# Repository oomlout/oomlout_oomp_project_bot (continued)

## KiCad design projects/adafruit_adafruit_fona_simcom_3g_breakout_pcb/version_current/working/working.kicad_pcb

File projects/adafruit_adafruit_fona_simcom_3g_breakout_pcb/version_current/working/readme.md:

# Adafruit-FONA-SIMCOM-3G-Breakout-PCB by adafruit  
This is a harvested standardized copy of a project from github.  
The original project can be found at:  
https://github.com/adafruit/Adafruit-FONA-SIMCOM-3G-Breakout-PCB  
Please consult that link for additional, details, files, and license information.  
Note: It was auto harvested and if the original repo had more than one board file or anything out of the ordinary the files here are likely not representative.

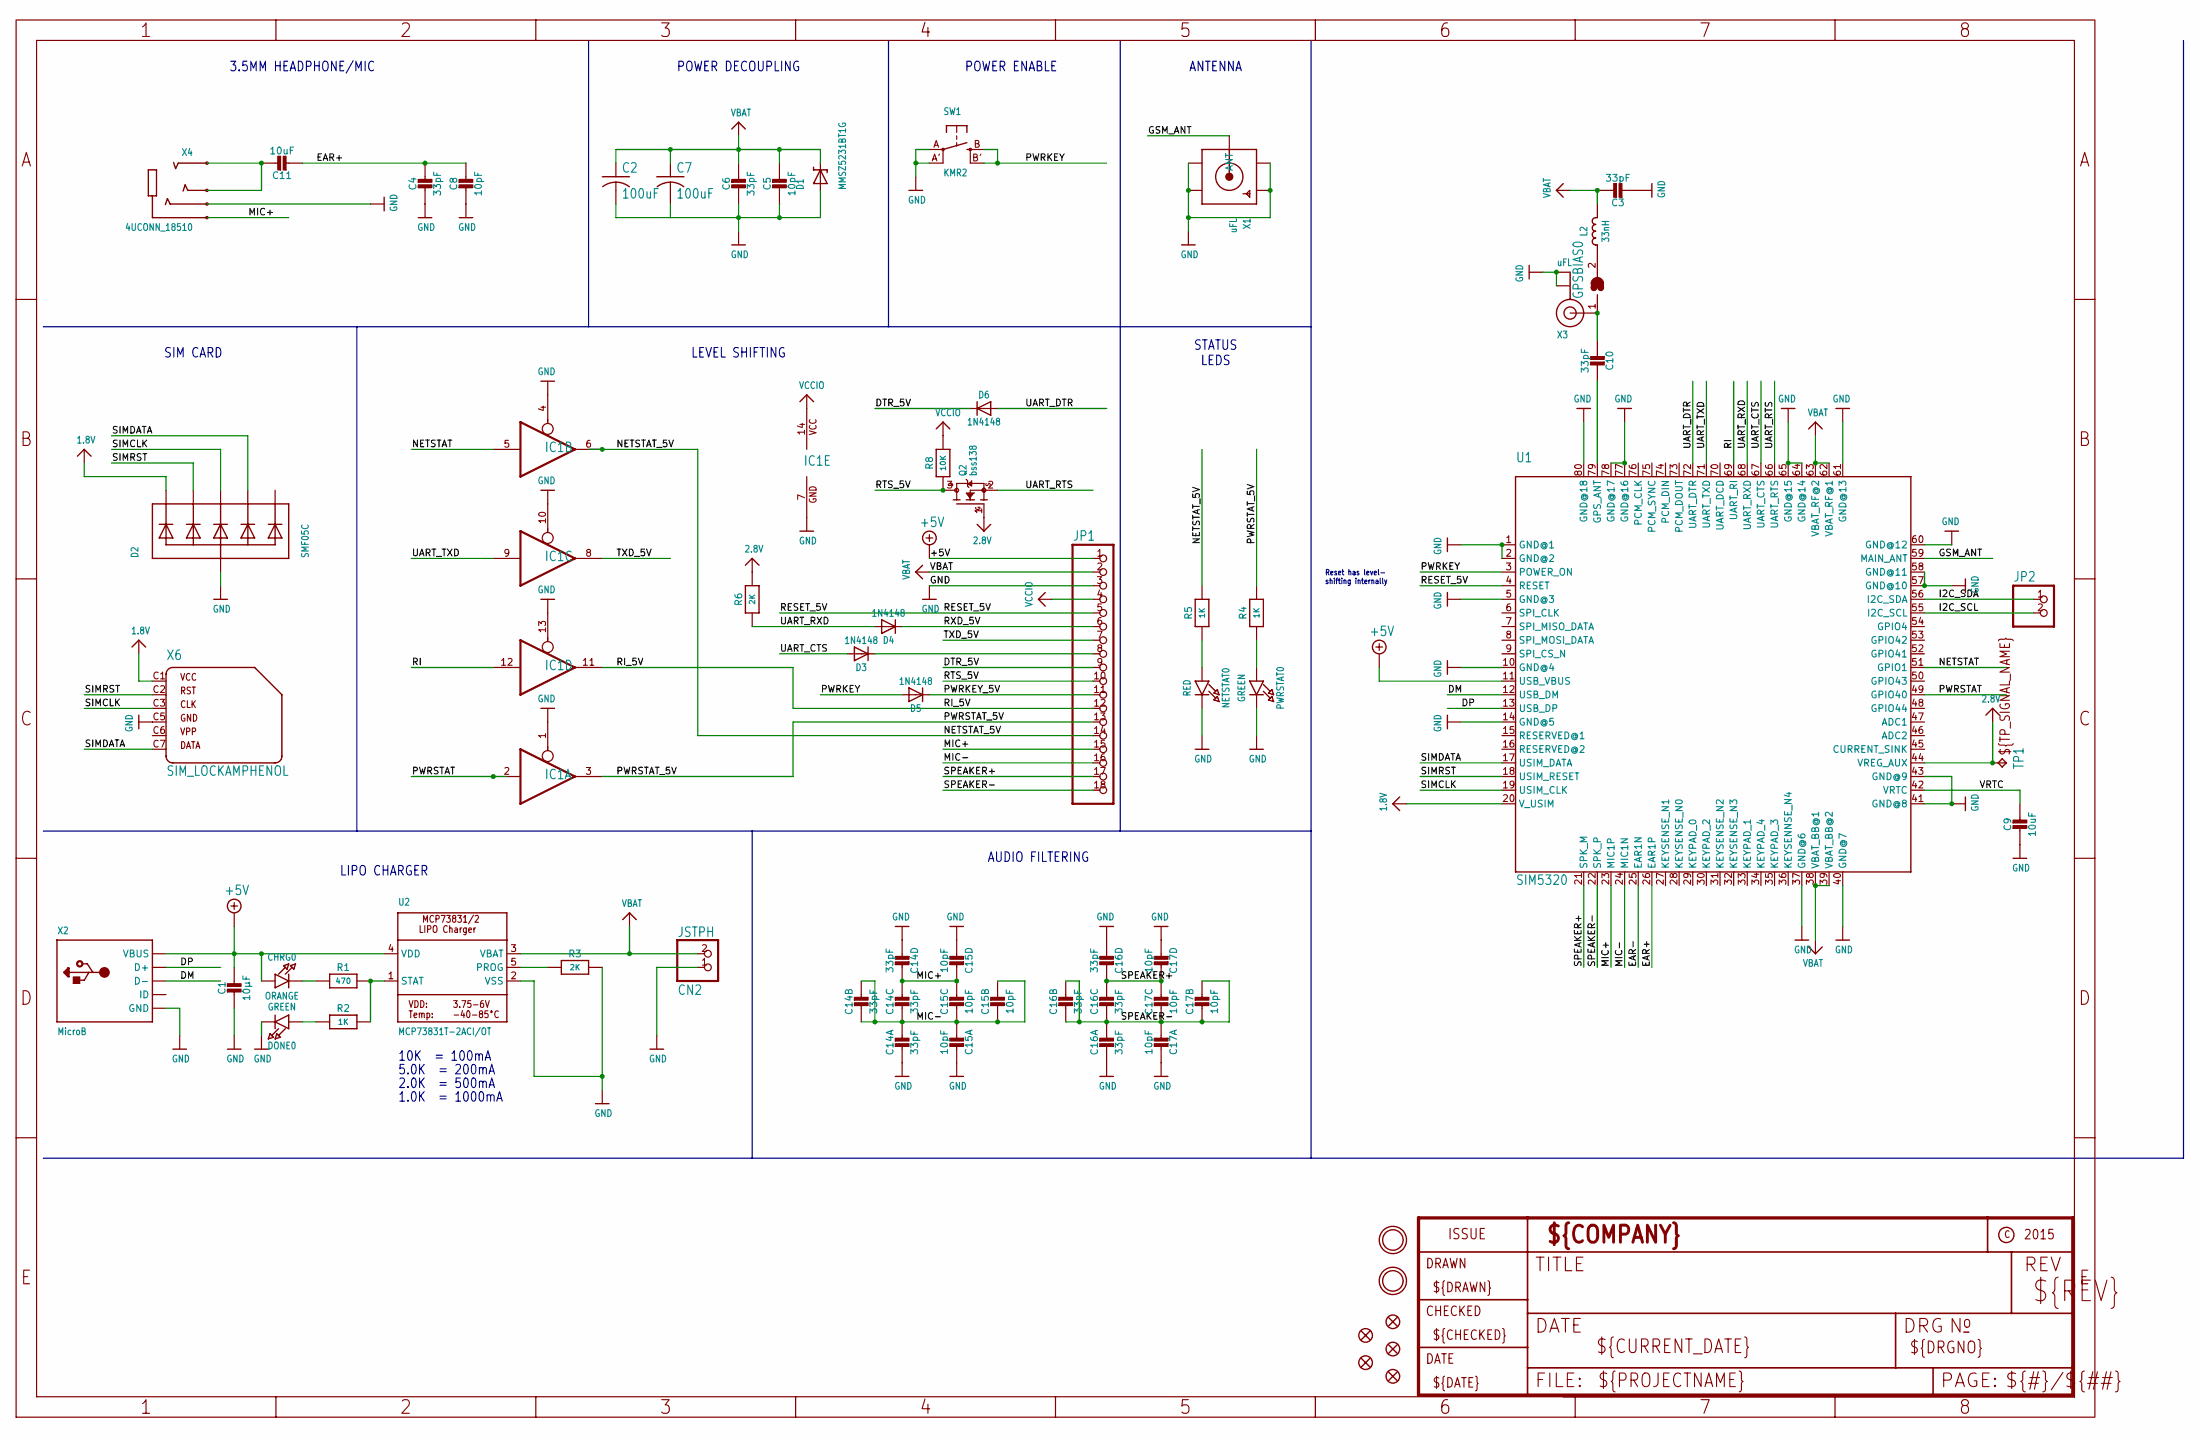
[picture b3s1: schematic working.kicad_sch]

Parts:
C1: 10µF; 0805-NO
C2, C7: 100uF; C1210
C3, C4, C6, C10: 33pF; 0805-NO
C5, C8: 10pF; 0805-NO
C9, C11: 10uF; 0805-NO
C14, C16: 33pF; RESPACK_4X0603
C15, C17: 10pF; RESPACK_4X0603
CHRG0: ORANGE; CHIPLED_0805_NOOUTLINE
CN2: JSTPH; JSTPH2
D1: MMSZ5231BT1G; SOD-123
D2: SMF05C; SOT363
D3, D4, D5, D6: 1N4148; SOD-323
DONE0: GREEN; CHIPLED_0805_NOOUTLINE
FID1, FID2, FID3, FID4, FID5: FIDUCIAL""; FIDUCIAL_1MM
GPSBIAS0: SOLDERJUMPER; SOLDERJUMPER_ARROW_NOPASTE
IC1: 74125PW; TSSOP14
JP1: HEADER-1X18; 1X18_ROUND70
JP2: HEADER-1X2ROUND; 1X02_ROUND
L2: 33nH; _0805MP
NETSTAT0: RED; CHIPLED_0805_NOOUTLINE
PWRSTAT0: GREEN; CHIPLED_0805_NOOUTLINE
Q2: bss138; SOT23-WIDE
R1: 470; 0805-NO
R2, R4, R5: 1K; 0805-NO
R3, R6: 2K; 0805-NO
R8: 10K; 0805-NO
SW1: KMR2; BTN_KMR2_4.6X2.8
TP1: TPTP11R; TP11R
U1: SIM5320
U2: MCP73831T-2ACI/OT; SOT23-5
U$33, U$34: MOUNTINGHOLE2.5; MOUNTINGHOLE_2.5_PLATED
X1: uFL; SMA_EDGELAUNCH_UFL
X2: MicroB; 4UCONN_20329
X3: uFL; U.FL
X4: 4UCONN_18510
X6: SIM_LOCKAMPHENOL; C707_10M006_512_2

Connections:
1.8V: D2.1 (C1), U1.20 (V_USIM), X6.C1 (1)
2.8V: Q2.1 (G), R6.2, TP1.TP, U1.44 (VREG_AUX)
+5V: C1.1, CHRG0.A, JP1.1, U1.11 (USB_VBUS), U2.4 (VDD), X2.VBUS
CTS_5V: D3.C, JP1.8
DM: U1.12 (USB_DM), X2.D-
DP: U1.13 (USB_DP), X2.D+
DTR_5V: D6.C, JP1.9
EAR+: C4.1, C8.1, C11.2, U1.26 (EAR1P)
EAR-: U1.25 (EAR1N)
GND: C1.2, C2.2, C3.2, C4.2, C5.2, C6.2, C7.2, C8.2, C9.2, C14.5 (2), C14.8 (2), C15.4 (1), C15.8 (2), C16.5 (2), C16.8 (2), C17.4 (1), C17.8 (2), CN2.1, D1.A, D2.2 (A), DONE0.C, IC1.1 (OE), IC1.4 (OE), IC1.7 (GND), IC1.10 (OE), IC1.13 (OE), JP1.3, NETSTAT0.C, PWRSTAT0.C, R3.2, SW1.A, SW1.A' (P1), U1.1 (GND@1), U1.2 (GND@2), U1.5 (GND@3), U1.10 (GND@4), U1.14 (GND@5), U1.37 (GND@6), U1.40 (GND@7), U1.41 (GND@8), U1.43 (GND@9), U1.57 (GND@10), U1.58 (GND@11), U1.60 (GND@12), U1.61 (GND@13), U1.64 (GND@14), U1.65 (GND@15), U1.77 (GND@16), U1.78 (GND@17), U1.80 (GND@18), U2.2 (VSS), X1.GND@1 (GND1), X1.GND@2 (GND2), X1.GND@3 (GND3), X1.GND@4 (GND4), X2.BASE@1 (GND), X2.BASE@2 (GND), X2.GND, X2.SPRT@1 (GND), X2.SPRT@2 (GND), X2.SPRT@3 (GND), X2.SPRT@4 (GND), X3.1 (GND@0), X3.2 (GND@1), X4.4-INNER_SLEEVE (RING1), X6.C5 (4)
GSM_ANT: U1.59 (MAIN_ANT), X1.P (ANT)
HP+: C11.1, X4.2-TIP (RING3), X4.3-OUTER_SLEEVE (RING2)
I2C_SCL: JP2.2, U1.55 (I2C_SCL)
I2C_SDA: JP2.1, U1.56 (I2C_SDA)
MIC+: C14.1, C14.2 (1), C15.1, C15.2 (1), JP1.15, U1.23 (MIC1P), X4.1-GND (TIP)
MIC-: C14.3 (1), C14.4 (1), C14.6 (2), C14.7 (2), C15.3 (1), C15.5 (2), C15.6 (2), C15.7 (2), JP1.16, U1.24 (MIC1N)
unnamed: CHRG0.C, R1.1
unnamed: R1.2, R2.2, U2.1 (STAT)
unnamed: C10.2, GPSBIAS0.1, X3.3 (SIGNAL)
unnamed: PWRSTAT0.A, R4.1
unnamed: R3.1, U2.5 (PROG)
unnamed: DONE0.A, R2.1
unnamed: C10.1, U1.79 (GPS_ANT)
unnamed: NETSTAT0.A, R5.1
unnamed: GPSBIAS0.2, L2.1
NETSTAT: IC1.5 (I), U1.51 (GPIO1)
NETSTAT_5V: IC1.6 (O), JP1.14, R5.2
PWRKEY: D5.A, SW1.B (S), SW1.B' (S1), U1.3 (POWER_ON)
PWRKEY_5V: D5.C, JP1.11
PWRSTAT: IC1.2 (I), U1.49 (GPIO40)
PWRSTAT_5V: IC1.3 (O), JP1.13, R4.2
RESET_5V: JP1.5, U1.4 (RESET)
RI: IC1.12 (I), U1.69 (UART_RI)
RI_5V: IC1.11 (O), JP1.12
RTS_5V: JP1.10, Q2.3 (D), R8.1
RXD_5V: D4.C, JP1.6
SIMCLK: D2.4 (C3), U1.19 (USIM_CLK), X6.C3 (3)
SIMDATA: D2.5 (C4), U1.17 (USIM_DATA), X6.C7 (6)
SIMRST: D2.3 (C2), U1.18 (USIM_RESET), X6.C2 (2)
SPEAKER+: C16.1, C16.2 (1), C17.1, C17.2 (1), JP1.17, U1.21 (SPK_M)
SPEAKER-: C16.3 (1), C16.4 (1), C16.6 (2), C16.7 (2), C17.3 (1), C17.5 (2), C17.6 (2), C17.7 (2), JP1.18, U1.22 (SPK_P)
TXD_5V: IC1.8 (O), JP1.7
UART_CTS: D3.A, U1.67 (UART_CTS)
UART_DTR: D6.A, U1.72 (UART_DTR)
UART_RTS: Q2.2 (S), U1.66 (UART_RTS)
UART_RXD: D4.A, R6.1, U1.68 (UART_RXD)
UART_TXD: IC1.9 (I), U1.71 (UART_TXD)
VBAT: C2.1, C3.1, C5.1, C6.1, C7.1, CN2.2, D1.C, JP1.2, L2.2, U1.38 (VBAT_BB@1), U1.39 (VBAT_BB@2), U1.62 (VBAT_RF@1), U1.63 (VBAT_RF@2), U2.3 (VBAT)
VCCIO: IC1.14 (VCC), JP1.4, R8.2
VRTC: C9.1, U1.42 (VRTC)

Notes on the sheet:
ANTENNA
STATUS LEDS
10K = 100mA
SIM CARD
POWER DECOUPLING
Reset has level- shifting internally
LIPO CHARGER
2.0K = 500mA
3.5MM HEADPHONE/MIC
POWER ENABLE
5.0K = 200mA
AUDIO FILTERING
LEVEL SHIFTING
1.0K = 1000mA

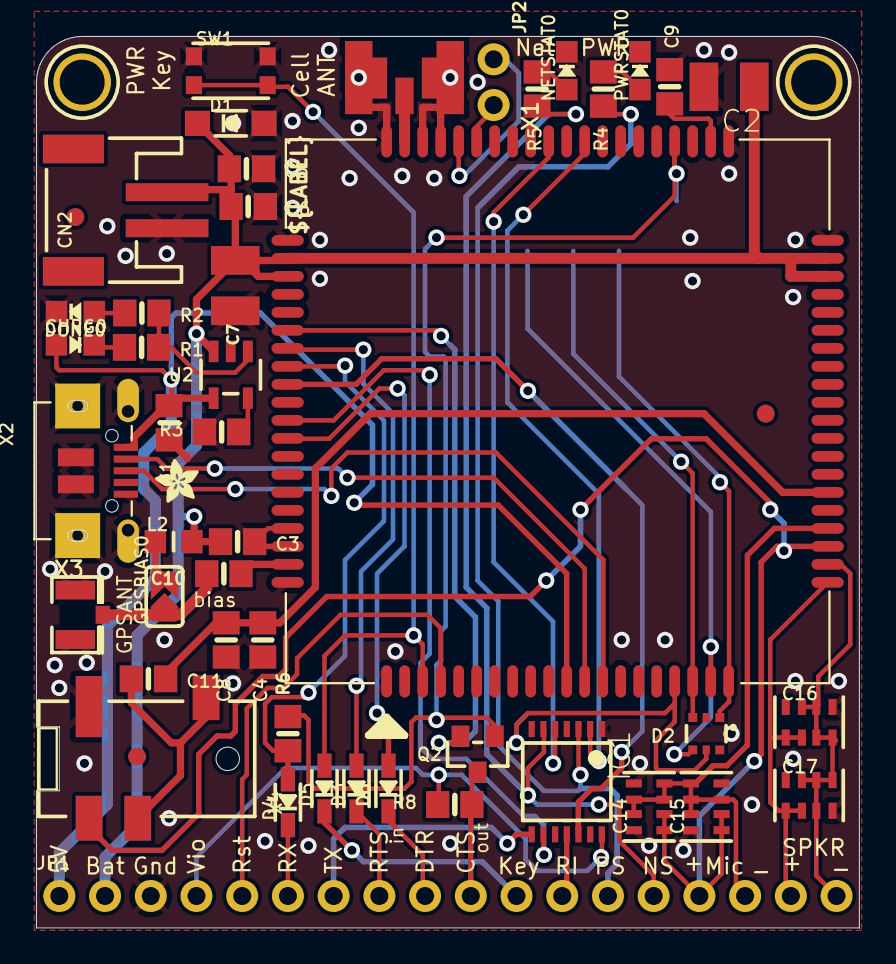
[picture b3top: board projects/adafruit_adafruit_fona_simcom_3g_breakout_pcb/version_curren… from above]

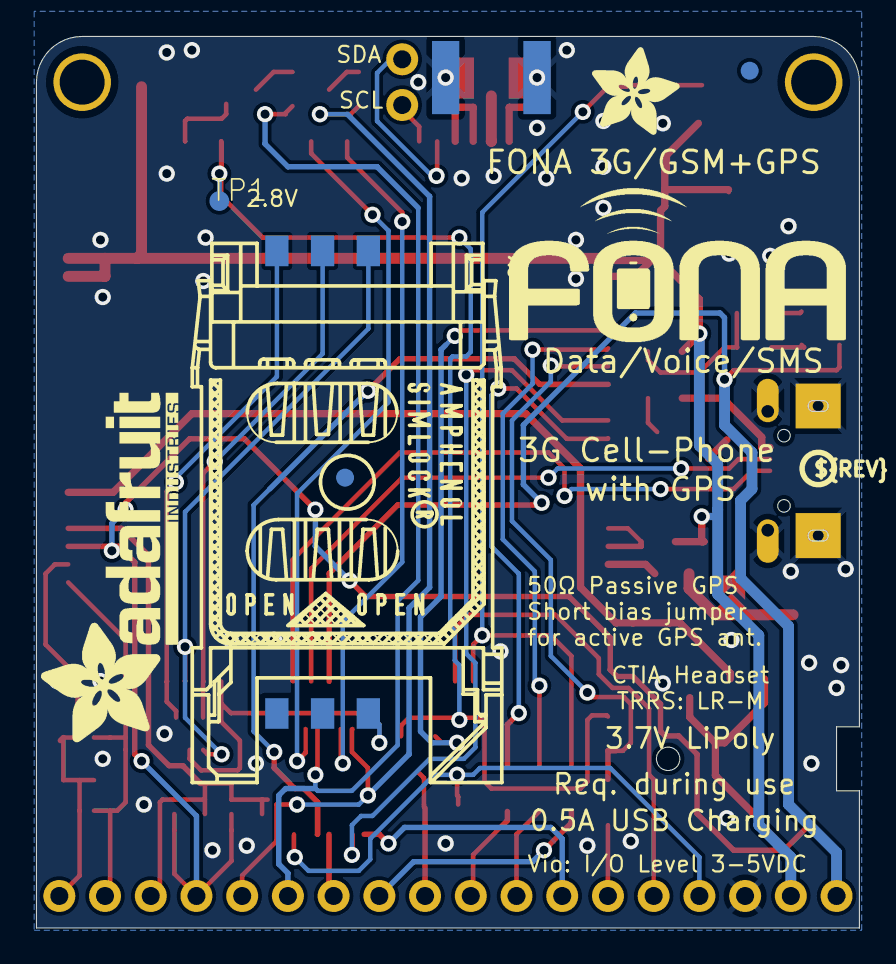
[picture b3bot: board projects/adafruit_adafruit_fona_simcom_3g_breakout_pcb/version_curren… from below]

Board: 2 copper layers, 45.7 x 49.5 mm, 60 parts (8 on the bottom side), 49 nets.

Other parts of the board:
U$21: ADAFRUIT_2.5MM
U$25: PCBFEAT-REV-040
U$26: FONA_LOGO
U$36: ADAFRUIT_5MM
U$42: ADAFRUIT_TEXT_20MM

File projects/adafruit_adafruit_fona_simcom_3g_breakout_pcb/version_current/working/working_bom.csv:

Row,Description,Part,References,Value,Footprint,Quantity Per PCB,Status,Datasheet
1,,CAP_4PACK1206,C15 C17,10pF,RESPACK_4X0603,2, ,
2,,CAP_CERAMIC0805-NOOUTLINE,C5 C8,10pF,0805-NO,2, ,
3,,CAP_CERAMIC0805-NOOUTLINE,C3 C4 C6 C10,33pF,0805-NO,4, ,
4,,CAP_4PACK1206,C14 C16,33pF,RESPACK_4X0603,2, ,
5,,CAP_CERAMIC0805-NOOUTLINE,C1 C9 C11,10µF,0805-NO,3, ,
6,,C-USC1210,C2 C7,100uF,C1210,2, ,
7,,LED0805_NOOUTLINE,CHRG0,ORANGE,CHIPLED_0805_NOOUTLINE,1, ,
8,,JST_2PIN,CN2,JSTPH,JSTPH2,1, ,
9,,DIODESOD-323,D3 D4 D5 D6,1N4148,SOD-323,4, ,
10,,DIODE-ZENERSOD123,D1,MMSZ5231BT1G,SOD-123,1, ,
11,,TVSARRAY_5LANE,D2,SMF05C,SOT363,1, ,
12,,LED0805_NOOUTLINE,DONE0 PWRSTAT0,GREEN,CHIPLED_0805_NOOUTLINE,2, ,
13,,74125PW,IC1,74125PW,TSSOP14,1, ,
14,,HEADER-1X18,JP1,HEADER-1X18,1X18_ROUND70,1, ,
15,,HEADER-1X2ROUND,JP2,HEADER-1X2ROUND,1X02_ROUND,1, ,
16,,INDUCTOR_0805MP,L2,33nH,_0805MP,1, ,
17,,LED0805_NOOUTLINE,NETSTAT0,RED,CHIPLED_0805_NOOUTLINE,1, ,
18,,MOSFET-NWIDE,Q2,bss138,SOT23-WIDE,1, ,
19,,RESISTOR0805_NOOUTLINE,R1,470,0805-NO,1, ,
20,,RESISTOR0805_NOOUTLINE,R2 R4 R5,1K,0805-NO,3, ,
21,,RESISTOR0805_NOOUTLINE,R3 R6,2K,0805-NO,2, ,
22,,RESISTOR0805_NOOUTLINE,R8,10K,0805-NO,1, ,
23,,SWITCH_TACT_SMT4.6X2.8,SW1,KMR2,BTN_KMR2_4.6X2.8,1, ,
24,,MCP73831/2,U2,MCP73831T-2ACI/OT,SOT23-5,1, ,
25,,GSM_SIM5320_LITERAL,U1,SIM5320,SIM5320,1, ,
26,,AUDIO_3.5MMJACK_4POL,X4,4UCONN_18510,4UCONN_18510,1, ,
27,,USBMICRO_20329,X2,MicroB,4UCONN_20329,1, ,
28,,SIM_LOCKAMPHENOL,X6,SIM_LOCKAMPHENOL,C707_10M006_512_2,1, ,
29,,SMACONNECTOR_EDGE_UFL,X1,uFL,SMA_EDGELAUNCH_UFL,1, ,
30,,ANTENNA_U.FL,X3,uFL,U.FL,1, ,





Project info:
Schematic:,working
Variant:,default
Revision:,
Date:,2023-08-02_17-08-33
KiCad Version:,7.0.6-7.0.6~ubuntu22.04.1
Statistics:
Component Groups:,30
Component Count:,46 (0 SMD/ 0 THT)
Fitted Components:,46 (0 SMD/ 0 THT)
Number of PCBs:,1
Total Components:,46

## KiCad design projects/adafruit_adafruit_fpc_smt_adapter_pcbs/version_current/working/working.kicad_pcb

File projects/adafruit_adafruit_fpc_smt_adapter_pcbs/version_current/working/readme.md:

# OOMP Project  
## Adafruit-FPC-SMT-Adapter-PCBs  by adafruit  
  
oomp key: oomp_projects_flat_adafruit_adafruit_fpc_smt_adapter_pcbs  
(snippet of original readme)  
  
-- Adafruit FPC SMT Adapter PCBs  
&nbsp;   
&nbsp;   
<br />  
Click to purchase from the Adafruit Shop:  
- [Adafruit FPC Stick - 20 Pin 0.5mm/1.0mm Pitch Adapter](https://www.adafruit.com/product/1325)  
- [Adafruit Multi-pitch FPC Adapter - 40 Pin 0.5/0.6/0.7/0.8/1.0mm](https://www.adafruit.com/product/1436)  
- [Adafruit 50 pin 0.5mm pitch FPC Adapter](https://www.adafruit.com/product/1492)  
  
Connect to 0.5mm, 1.0mm and even some 2.0mm pitch connectors that you may run across with an FPC stick. We designed this for use in house, to quickly connect to FPCs we need to test. But we also thought it might be useful for our customers. On either side is a 20 pin 0.5 or 1.0mm pitch connector with long pads and one very long 'mechanical' pad. Each pad is broken out to a 20-pin long 0.1" spaced header. It can accommodate most ZIF and snap connectors and will make prototyping much easier on you!  
  
You will roll lucky 7's and connect to nearly any kind of FPC/flex cable with Ladyada's Super Lucky 40-pin FPC to breadboard adapter plate. You get 40 pads of 0.5mm, 0.6mm, 0.7mm, 0.8mm or 1.0mm. It may even work for some 2.0mm pitch connectors. We designed this for use in house, to quickly connect to FP  
  full source readme at [readme_src.md](readme_src.md)  
  
source repo at: [https://github.com/adafruit/Adafruit-FPC-SMT-Adapter-PCBs](https://github.com/adafruit/Adafruit-FPC-SMT-Adapter-PCBs)  
## Board  

## Schematic  

[schematic pdf](working_schematic.pdf)  
## Images

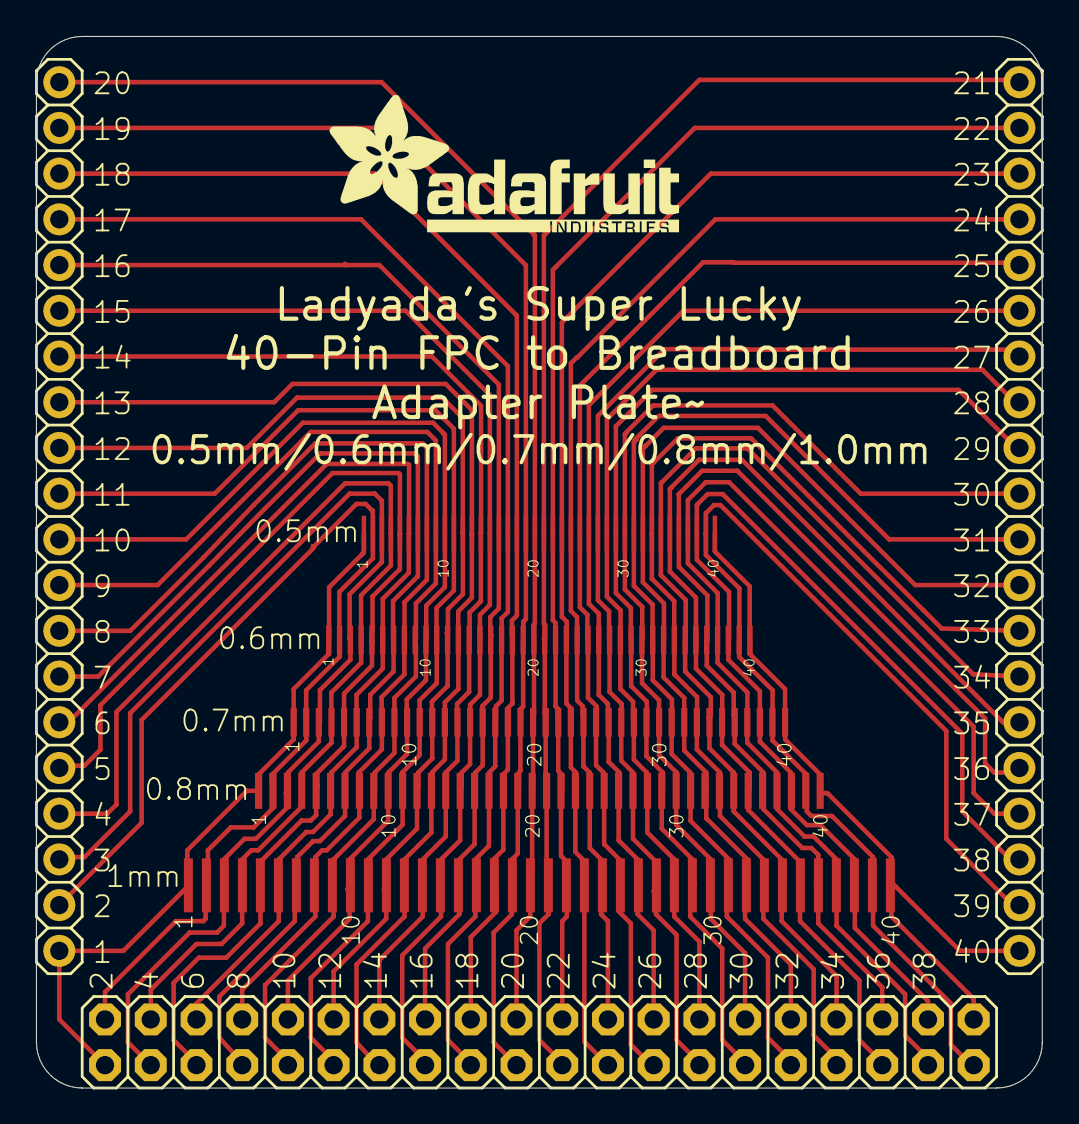
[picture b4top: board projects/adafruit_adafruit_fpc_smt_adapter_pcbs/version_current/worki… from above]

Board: 16 copper layers, 55.9 x 58.4 mm, 9 parts (0 on the bottom side), 40 nets.

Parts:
CON1: PINHD-1X40-0.5MM; 1X40-0.5MM
JP1: 2X20-BIG
JP2, JP3: 1X20-BIG
U$1: PINHD-1X40-0.6MM; 1X40-0.6MM
U$2: PINHD-1X40-0.7MM; 1X40-0.7MM
U$3: PINHD-1X40-0.8MM; 1X40-0.8MM
U$4: PINHD-1X40-1MM; 1X40-1MM
U$5: ADAFRUIT_TEXT_20MM

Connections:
unnamed: CON1.1, JP1.1, JP2.1, U$1.1, U$2.1, U$3.1, U$4.1
unnamed: CON1.2, JP1.2, JP2.2, U$1.2, U$2.2, U$3.2, U$4.2
unnamed: CON1.3, JP1.3, JP2.3, U$1.3, U$2.3, U$3.3, U$4.3
unnamed: CON1.4, JP1.4, JP2.4, U$1.4, U$2.4, U$3.4, U$4.4
unnamed: CON1.5, JP1.5, JP2.5, U$1.5, U$2.5, U$3.5, U$4.5
unnamed: CON1.6, JP1.6, JP2.6, U$1.6, U$2.6, U$3.6, U$4.6
unnamed: CON1.7, JP1.7, JP2.7, U$1.7, U$2.7, U$3.7, U$4.7
unnamed: CON1.8, JP1.8, JP2.8, U$1.8, U$2.8, U$3.8, U$4.8
unnamed: CON1.9, JP1.9, JP2.9, U$1.9, U$2.9, U$3.9, U$4.9
unnamed: CON1.10, JP1.10, JP2.10, U$1.10, U$2.10, U$3.10, U$4.10
unnamed: CON1.11, JP1.11, JP2.11, U$1.11, U$2.11, U$3.11, U$4.11
unnamed: CON1.12, JP1.12, JP2.12, U$1.12, U$2.12, U$3.12, U$4.12
unnamed: CON1.13, JP1.13, JP2.13, U$1.13, U$2.13, U$3.13, U$4.13
unnamed: CON1.14, JP1.14, JP2.14, U$1.14, U$2.14, U$3.14, U$4.14
unnamed: CON1.15, JP1.15, JP2.15, U$1.15, U$2.15, U$3.15, U$4.15
unnamed: CON1.16, JP1.16, JP2.16, U$1.16, U$2.16, U$3.16, U$4.16
unnamed: CON1.17, JP1.17, JP2.17, U$1.17, U$2.17, U$3.17, U$4.17
unnamed: CON1.18, JP1.18, JP2.18, U$1.18, U$2.18, U$3.18, U$4.18
unnamed: CON1.19, JP1.19, JP2.19, U$1.19, U$2.19, U$3.19, U$4.19
unnamed: CON1.20, JP1.20, JP2.20, U$1.20, U$2.20, U$3.20, U$4.20
unnamed: CON1.21, JP1.21, JP3.1, U$1.21, U$2.21, U$3.21, U$4.21
unnamed: CON1.22, JP1.22, JP3.2, U$1.22, U$2.22, U$3.22, U$4.22
unnamed: CON1.23, JP1.23, JP3.3, U$1.23, U$2.23, U$3.23, U$4.23
unnamed: CON1.24, JP1.24, JP3.4, U$1.24, U$2.24, U$3.24, U$4.24
unnamed: CON1.25, JP1.25, JP3.5, U$1.25, U$2.25, U$3.25, U$4.25
unnamed: CON1.26, JP1.26, JP3.6, U$1.26, U$2.26, U$3.26, U$4.26
unnamed: CON1.27, JP1.27, JP3.7, U$1.27, U$2.27, U$3.27, U$4.27
unnamed: CON1.28, JP1.28, JP3.8, U$1.28, U$2.28, U$3.28, U$4.28
unnamed: CON1.29, JP1.29, JP3.9, U$1.29, U$2.29, U$3.29, U$4.29
unnamed: CON1.30, JP1.30, JP3.10, U$1.30, U$2.30, U$3.30, U$4.30
unnamed: CON1.31, JP1.31, JP3.11, U$1.31, U$2.31, U$3.31, U$4.31
unnamed: CON1.32, JP1.32, JP3.12, U$1.32, U$2.32, U$3.32, U$4.32
unnamed: CON1.33, JP1.33, JP3.13, U$1.33, U$2.33, U$3.33, U$4.33
unnamed: CON1.34, JP1.34, JP3.14, U$1.34, U$2.34, U$3.34, U$4.34
unnamed: CON1.35, JP1.35, JP3.15, U$1.35, U$2.35, U$3.35, U$4.35
unnamed: CON1.36, JP1.36, JP3.16, U$1.36, U$2.36, U$3.36, U$4.36
unnamed: CON1.37, JP1.37, JP3.17, U$1.37, U$2.37, U$3.37, U$4.37
unnamed: CON1.38, JP1.38, JP3.18, U$1.38, U$2.38, U$3.38, U$4.38
unnamed: CON1.39, JP1.39, JP3.19, U$1.39, U$2.39, U$3.39, U$4.39
unnamed: CON1.40, JP1.40, JP3.20, U$1.40, U$2.40, U$3.40, U$4.40

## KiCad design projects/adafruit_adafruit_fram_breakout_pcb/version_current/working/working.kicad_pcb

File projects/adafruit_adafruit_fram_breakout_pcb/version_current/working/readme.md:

# OOMP Project  
## Adafruit-FRAM-Breakout-PCB  by adafruit  
  
oomp key: oomp_projects_flat_adafruit_adafruit_fram_breakout_pcb  
(snippet of original readme)  
  
- Adafruit FRAM Breakout PCBs  
  
&nbsp; <br />  
Click to purchase from the Adafruit Shop:  
- [I2C Version](https://www.adafruit.com/product/1895)  
- [SPI Version](https://www.adafruit.com/product/1897)  
- [2 Mbit SPI Version](https://www.adafruit.com/product/4718)  
- [4 Mbit SPI Version](https://www.adafruit.com/product/4719)  

FRAM, or Ferroelectric Ram, is pretty cool! It's similar to Dynamic random-access memory, only with a ferroelectric layer instead of a dielectric layer. This gives it stable handling (the bytes you write are non-volatile) with dynamic responsiveness (you can write them very fast!)  
  
Now, with our FRAM breakout boards, you can add some FRAM storage to your next DIY project. FRAM allows for a lower power usage and a faster write performance. It's excellent for low-power or inconsistent-power datalogging or data buffering where you want to stream data fast while also keeping the data when there's no power. Unlike Flash or EEPROM there's no pages to worry about. Each byte can be read/written 10,000,000,000,000 times so you don't have to worry too much about wear leveling.  
  
These particular FRAM chips have 64 Kbits (8 KBytes) of storage, interfaces using SPI or I2C (select the correct board for the correct bus, they cannot do both!), and can run at up to 20MHz SPI   
  full source readme at [readme_src.md](readme_src.md)  
  
source repo at: [https://github.com/adafruit/Adafruit-FRAM-Breakout-PCB](https://github.com/adafruit/Adafruit-FRAM-Breakout-PCB)  
## Board  

## Schematic  

[schematic pdf](working_schematic.pdf)  
## Images

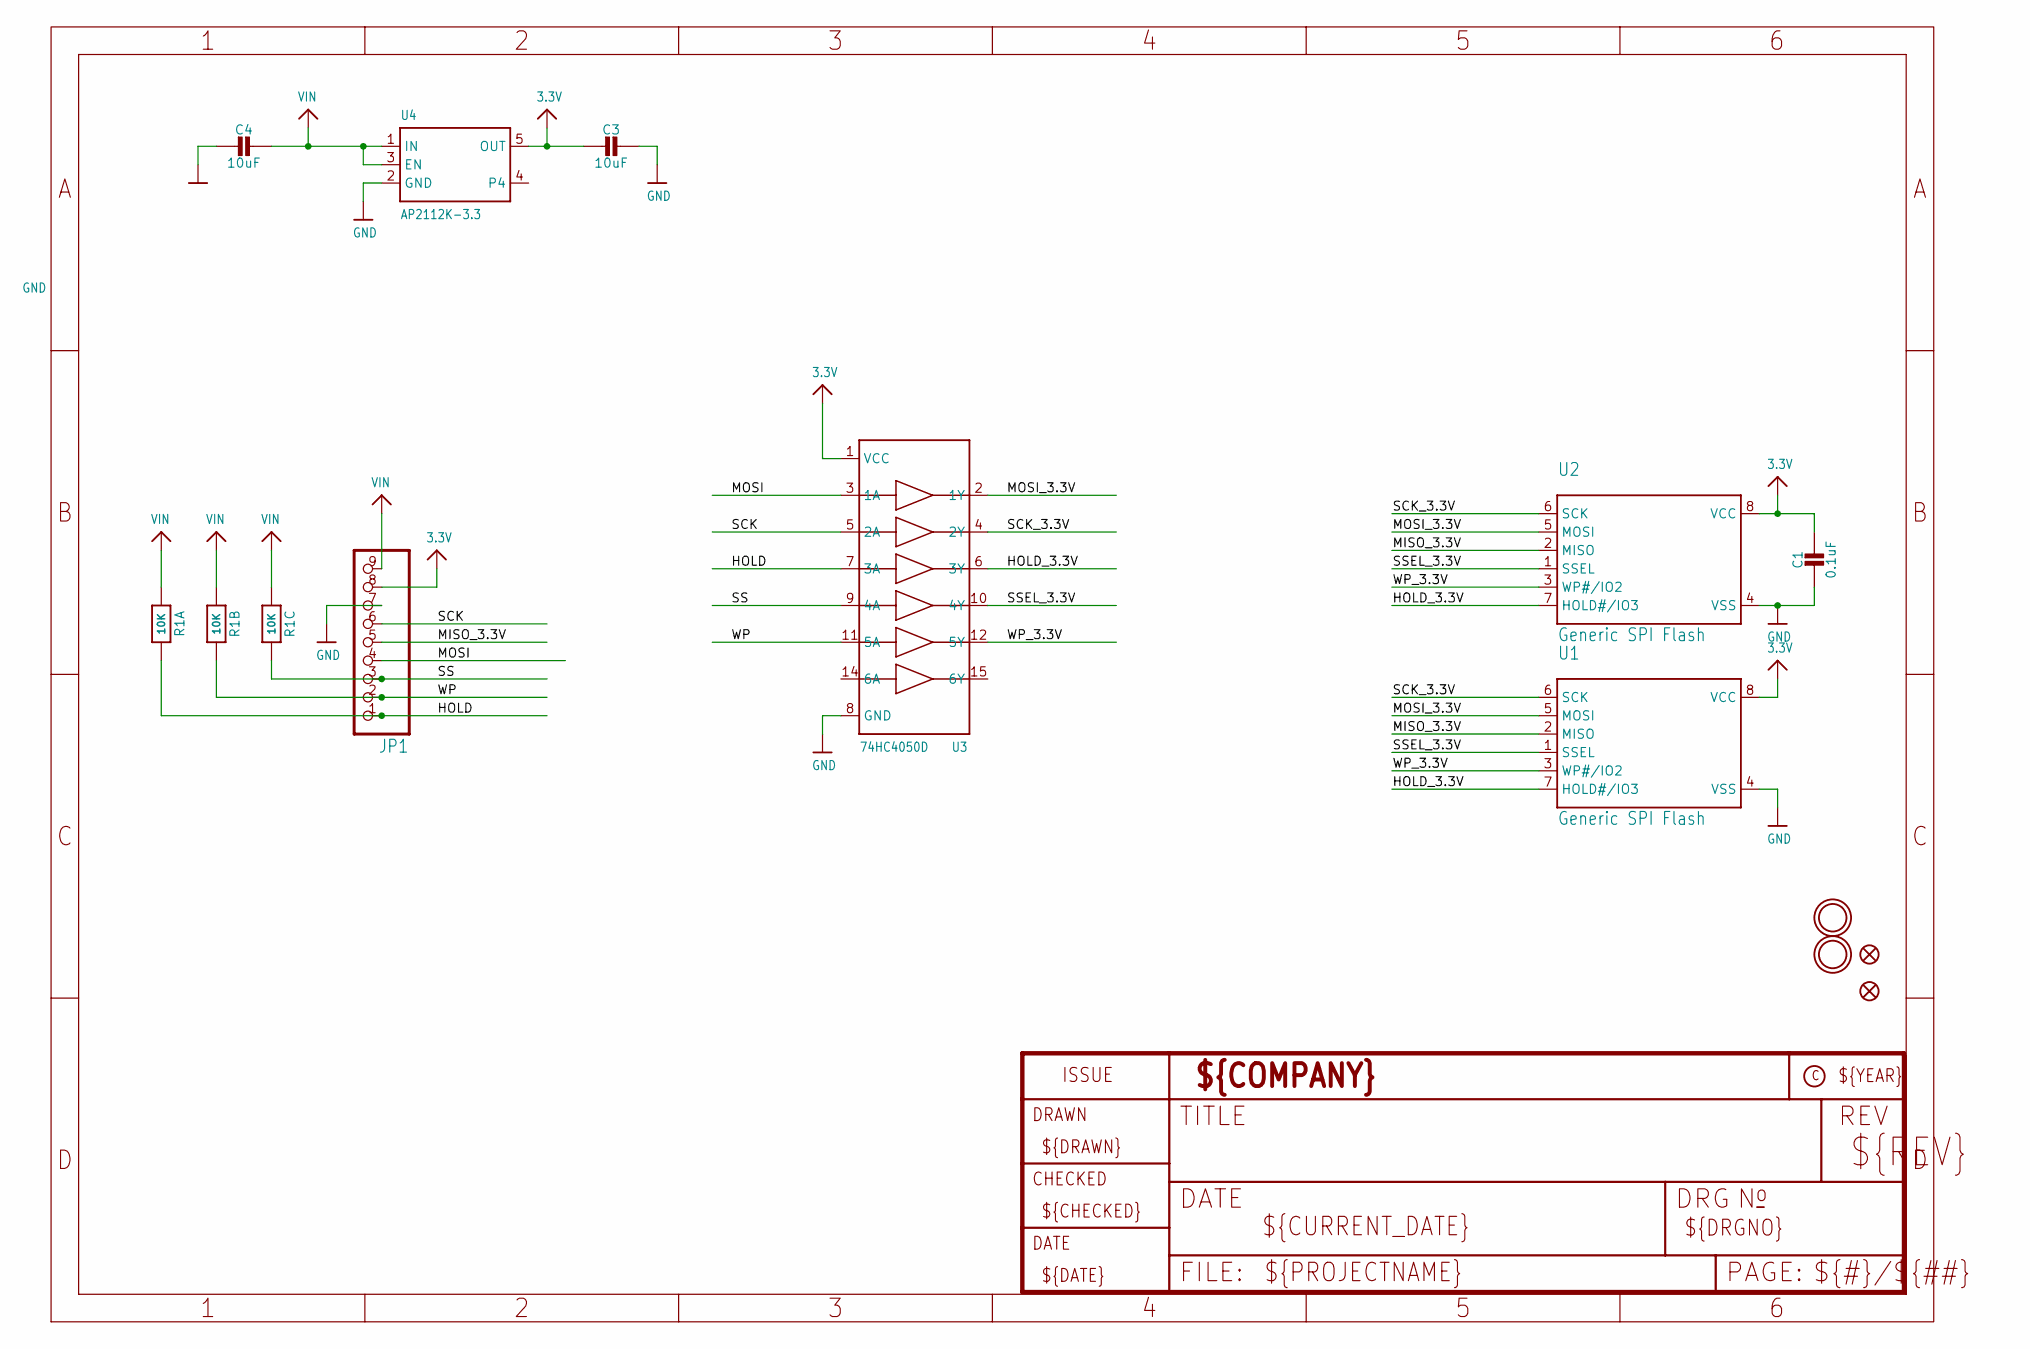
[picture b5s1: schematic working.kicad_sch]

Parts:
C1: 0.1uF; 0603-NO
C3, C4: 10uF; 0805-NO
FID2, FID3: FIDUCIAL_1MM
JP1: HEADER-1X970MIL; 1X09_ROUND_70
R1: 10K; RESPACK_4X0603
U1: Generic SPI Flash; SOIC8_208MIL
U2: Generic SPI Flash; USON8
U3: 74HC4050D; TSSOP16
U4: AP2112K-3.3; SOT23-5
U$16, U$17: MOUNTINGHOLE2.5; MOUNTINGHOLE_2.5_PLATED

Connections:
3.3V: C1.1, C3.2, JP1.8, U1.8 (VCC), U2.8 (VCC), U3.1 (VCC), U4.5 (OUT)
GND: C1.2, C3.1, C4.2, JP1.7, U1.4 (VSS), U2.4 (VSS), U3.8 (GND), U4.2 (GND)
HOLD: JP1.1, R1.8 (2), U3.7 (3A)
HOLD_3.3V: U1.7 (HOLD#/IO3), U2.7 (HOLD#/IO3), U3.6 (3Y)
MISO_3.3V: JP1.5, U1.2 (MISO), U2.2 (MISO)
MOSI: JP1.4, U3.3 (1A)
MOSI_3.3V: U1.5 (MOSI), U2.5 (MOSI), U3.2 (1Y)
SCK: JP1.6, U3.5 (2A)
SCK_3.3V: U1.6 (SCK), U2.6 (SCK), U3.4 (2Y)
SS: JP1.3, R1.6 (2), U3.9 (4A)
SSEL_3.3V: U1.1 (SSEL), U2.1 (SSEL), U3.10 (4Y)
VIN: C4.1, JP1.9, R1.1, R1.2 (1), R1.3 (1), U4.1 (IN), U4.3 (EN)
WP: JP1.2, R1.7 (2), U3.11 (5A)
WP_3.3V: U1.3 (WP#/IO2), U2.3 (WP#/IO2), U3.12 (5Y)

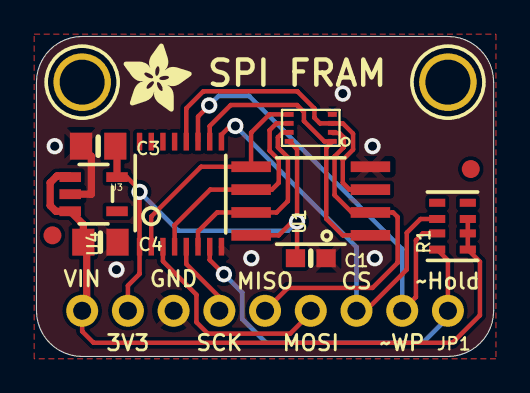
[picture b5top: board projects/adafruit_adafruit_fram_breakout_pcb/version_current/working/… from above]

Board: 2 copper layers, 25.4 x 17.8 mm, 15 parts (1 on the bottom side), 14 nets.

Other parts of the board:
U$19: ADAFRUIT_3.5MM
U$21: PCBFEAT-REV-040

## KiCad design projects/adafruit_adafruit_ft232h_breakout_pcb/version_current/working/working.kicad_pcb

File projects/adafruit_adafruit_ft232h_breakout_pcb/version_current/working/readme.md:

# OOMP Project  
## Adafruit-FT232H-Breakout-PCB  by adafruit  
  
oomp key: oomp_projects_flat_adafruit_adafruit_ft232h_breakout_pcb  
(snippet of original readme)  
  
-- Adafruit FT232H Breakout PCB  
<a href="http://www.adafruit.com/products/2264"><br/>  
Click here to purchase one from the Adafruit shop</a>  
  
Wouldn't it be cool to drive a tiny OLED display, read a color sensor, or even just flash some LEDs directly from your computer?  Sure you can program an Arduino or Trinket to talk to these devices and your computer, but why can't your computer just talk to those devices and sensors itself?  Well, now your computer can talk to devices using the Adafruit FT232H breakout board!  
  
What can the FT232H chip do?  This chip from FTDI is similar to their USB to serial converter chips but adds a 'multi-protocol synchronous serial engine' which allows it to speak many common protocols like SPI, I2C, serial UART, JTAG, and more!  There's even a handful of digital GPIO pins that you can read and write to do things like flash LEDs, read switches or buttons, and more.  The FT232H breakout is like adding a little swiss army knife for serial protocols to your computer!  
  
PCB files for the Adafruit FT232H Breakout. The format is EagleCAD schematic and board layout  
- http://www.adafruit.com/products/2264  
  
--- License  
  
Adafruit invests time and resources providing this open source design, please support Adafruit and open-source hardware by purchasing products from [Adafruit](https://www.adafruit.com)!  
  
All text above must be included in any redistribution  
  
Designed by Limor Fried/Ladyada for Adafruit Industr  
  full source readme at [readme_src.md](readme_src.md)  
  
source repo at: [https://github.com/adafruit/Adafruit-FT232H-Breakout-PCB](https://github.com/adafruit/Adafruit-FT232H-Breakout-PCB)  
## Board  

## Schematic  

[schematic pdf](working_schematic.pdf)  
## Images

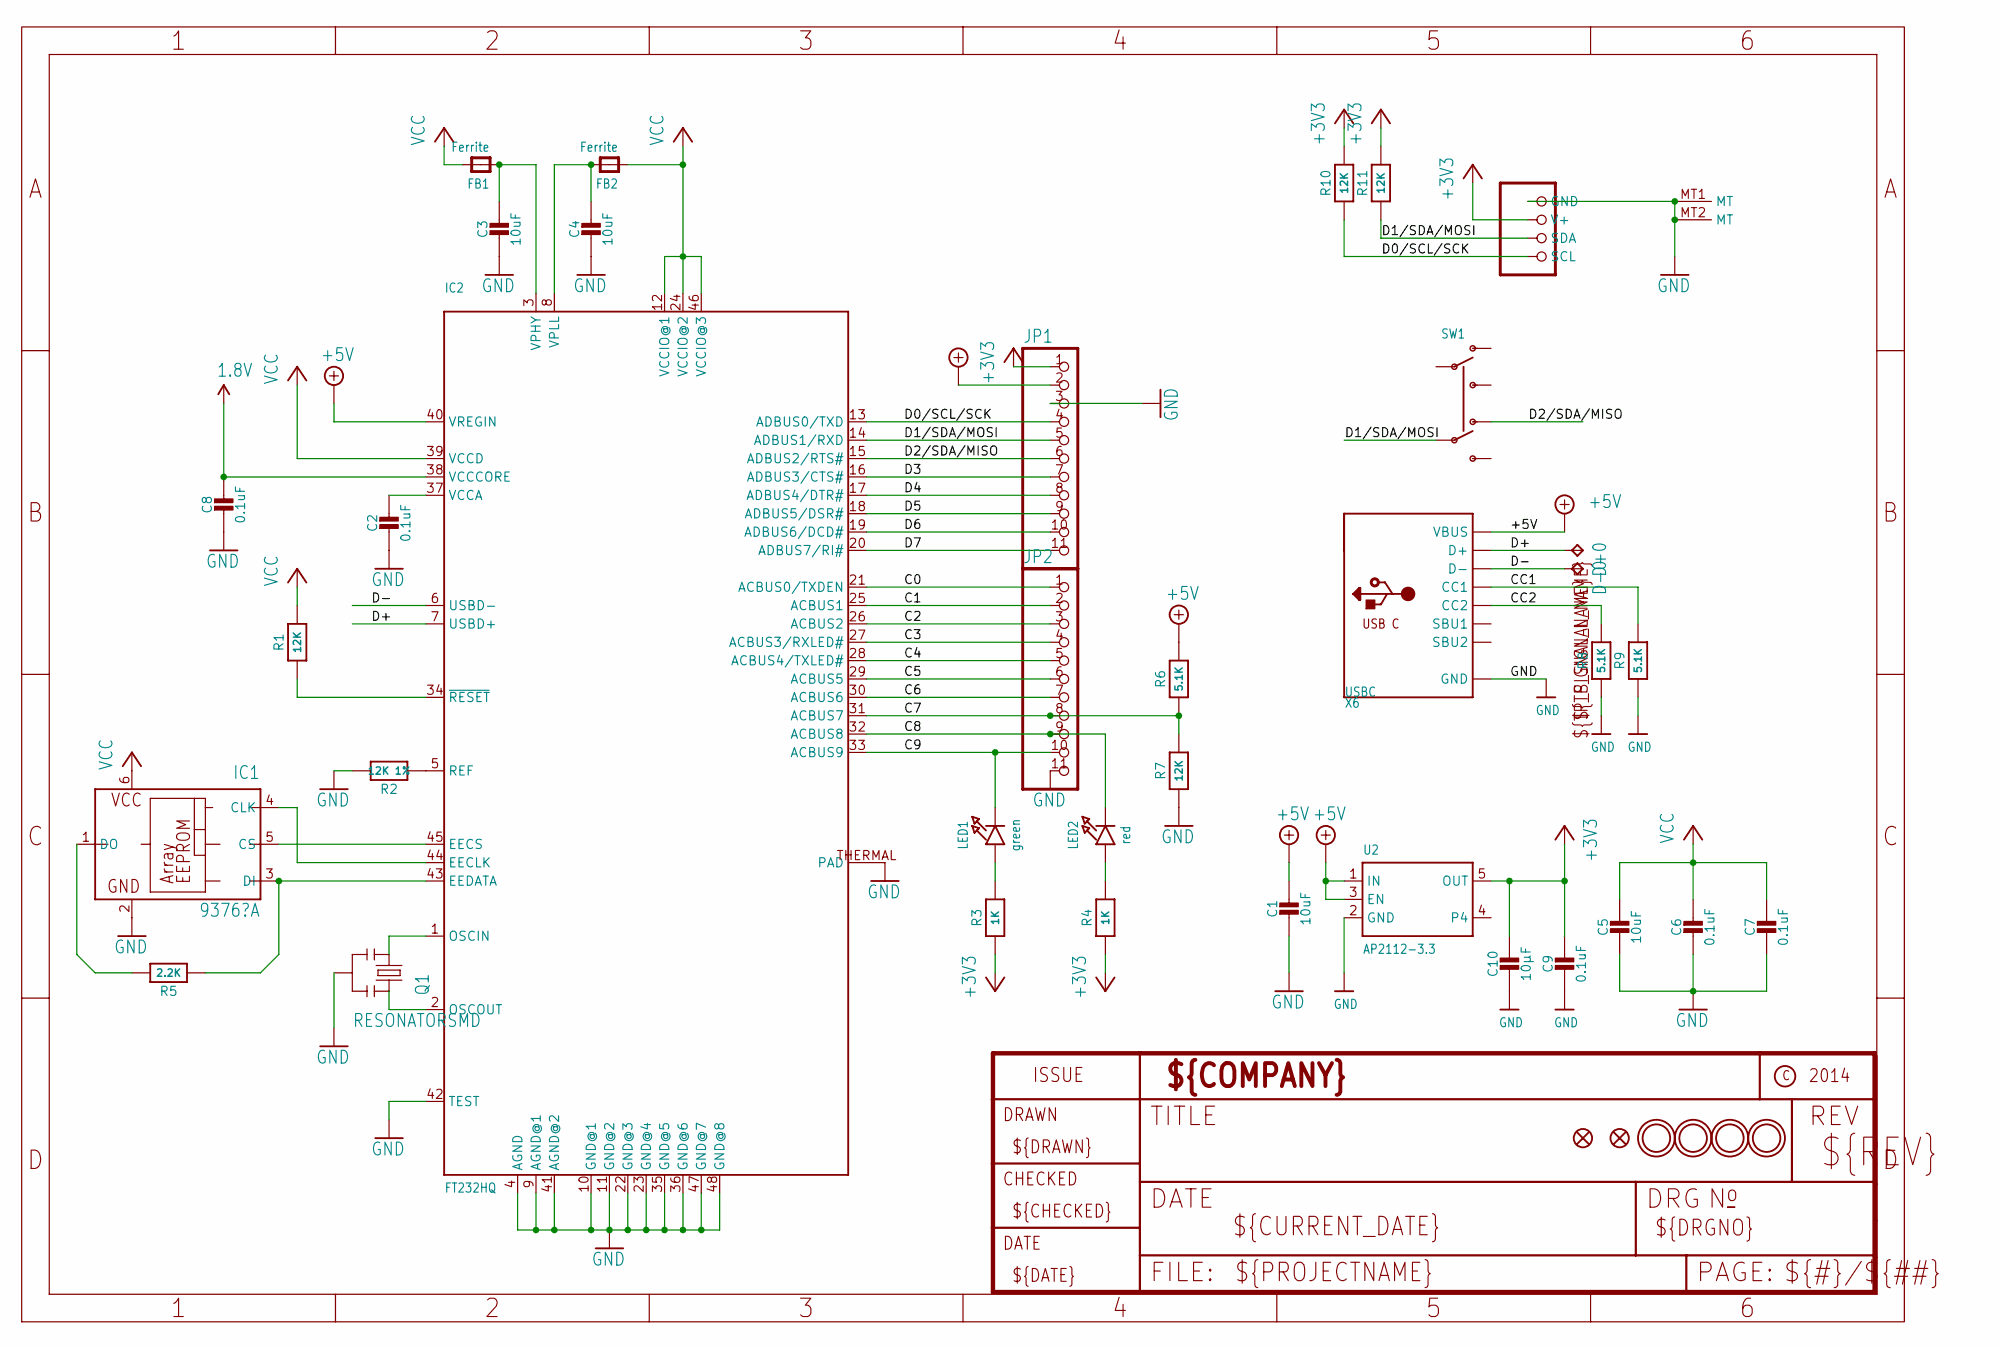
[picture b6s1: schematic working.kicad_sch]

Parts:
C1, C3, C4, C5: 10uF; 0805-NO
C2, C6, C7, C8, C9: 0.1uF; 0603-NO
C10: 10µF; 0805-NO
CONN1: STEMMA_I2C_QT; JST_SH4
D+0: TPTP17R; TP17R
D-0: TPTP17R; TP17R
FB1, FB2: Ferrite; _0805
FID1, FID2: FIDUCIAL""; FIDUCIAL_1MM
IC1: 9376?A; SOT23-6
IC2: FT232HQ; QFN48_8MM
JP1, JP2: HEADER-1X11; 1X11_ROUND
LED1: green; CHIPLED_0805_NOOUTLINE
LED2: red; CHIPLED_0805_NOOUTLINE
Q1: RESONATORSMD; RESONATOR-SMD
R1, R7, R10, R11: 12K; 0603-NO
R2: 12K 1%; 0603-NO
R3, R4: 1K; 0603-NO
R5: 2.2K; 0603-NO
R6, R8, R9: 5.1K; 0603-NO
SW1: SWITCH_DPDTEG1390; EG1390
U2: AP2112-3.3; SOT23-5
U$4, U$5, U$6, U$7: MOUNTINGHOLE2.5; MOUNTINGHOLE_2.5_PLATED
X6: USBC; USB_C_CUSB31-CFM2AX-01-X

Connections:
1.8V: C8.1, IC2.38 (VCCCORE)
+3V3: C9.1, C10.1, CONN1.2 (V+), JP1.1, R3.1, R4.1, R10.2, R11.2, U2.5 (OUT)
+5V: C1.1, IC2.40 (VREGIN), JP1.2, R6.2, U2.1 (IN), U2.3 (EN), X6.A4B9 (VBUS), X6.B4A9 (VBUS)
C0: IC2.21 (ACBUS0/TXDEN), JP2.1
C1: IC2.25 (ACBUS1), JP2.2
C2: IC2.26 (ACBUS2), JP2.3
C3: IC2.27 (ACBUS3/RXLED#), JP2.4
C4: IC2.28 (ACBUS4/TXLED#), JP2.5
C5: IC2.29 (ACBUS5), JP2.6
C6: IC2.30 (ACBUS6), JP2.7
C7: IC2.31 (ACBUS7), JP2.8, R6.1, R7.2
C8: IC2.32 (ACBUS8), JP2.9, LED2.C
C9: IC2.33 (ACBUS9), JP2.10, LED1.C
CC1: R9.2, X6.A5 (CC1)
CC2: R8.2, X6.B5 (CC2)
D0/SCL/SCK: CONN1.4 (SCL), IC2.13 (ADBUS0/TXD), JP1.4, R10.1
D1/SDA/MOSI: CONN1.3 (SDA), IC2.14 (ADBUS1/RXD), JP1.5, R11.1, SW1.P2
D2/SDA/MISO: IC2.15 (ADBUS2/RTS#), JP1.6, SW1.O2
D3: IC2.16 (ADBUS3/CTS#), JP1.7
D4: IC2.17 (ADBUS4/DTR#), JP1.8
D5: IC2.18 (ADBUS5/DSR#), JP1.9
D6: IC2.19 (ADBUS6/DCD#), JP1.10
D7: IC2.20 (ADBUS7/RI#), JP1.11
D+: D+0.TP, IC2.7 (USBD+), X6.A6 (D+), X6.B6 (D+)
D-: D-0.TP, IC2.6 (USBD-), X6.A7 (D-), X6.B7 (D-)
GND: C1.2, C2.2, C3.2, C4.2, C5.2, C6.2, C7.2, C8.2, C9.2, C10.2, CONN1.1 (GND), CONN1.MT1 (MT), CONN1.MT2 (MT), IC1.2 (GND), IC2.4 (AGND), IC2.9 (AGND@1), IC2.10 (GND@1), IC2.11 (GND@2), IC2.22 (GND@3), IC2.23 (GND@4), IC2.35 (GND@5), IC2.36 (GND@6), IC2.41 (AGND@2), IC2.42 (TEST), IC2.47 (GND@7), IC2.48 (GND@8), IC2.THERMAL (PAD), JP1.3, JP2.11, Q1.2, R2.2, R7.1, R8.1, R9.1, U2.2 (GND), X6.A1B12 (GND), X6.B1A12 (GND)
unnamed: IC2.1 (OSCIN), Q1.1
unnamed: IC2.2 (OSCOUT), Q1.3
unnamed: IC2.5 (REF), R2.1
unnamed: LED2.A, R4.2
unnamed: IC2.34 (~RESET), R1.1
unnamed: LED1.A, R3.2
unnamed: IC1.3 (DI), IC2.43 (EEDATA), R5.1
unnamed: IC1.5 (CS), IC2.45 (EECS)
unnamed: IC1.4 (CLK), IC2.44 (EECLK)
unnamed: IC1.1 (DO), R5.2
VCC: C5.1, C6.1, C7.1, FB1.2, FB2.1, IC1.6 (VCC), IC2.12 (VCCIO@1), IC2.24 (VCCIO@2), IC2.39 (VCCD), IC2.46 (VCCIO@3), R1.2
VCCA: C2.1, IC2.37 (VCCA)
VPHY: C3.1, FB1.1, IC2.3 (VPHY)
VPLL: C4.1, FB2.2, IC2.8 (VPLL)

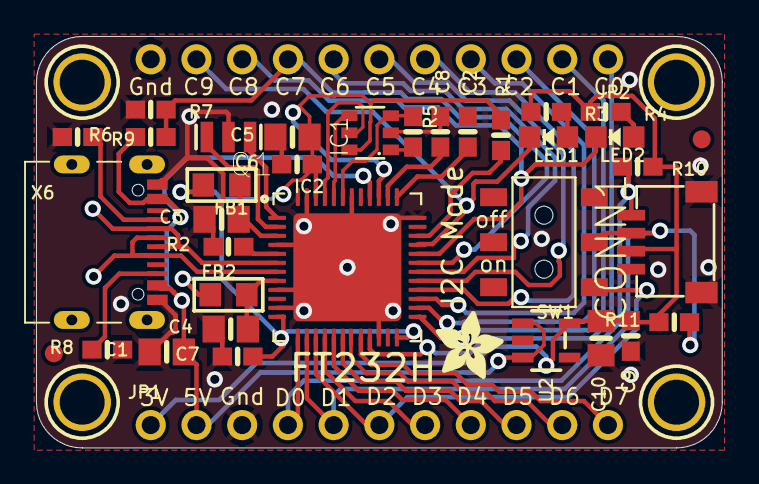
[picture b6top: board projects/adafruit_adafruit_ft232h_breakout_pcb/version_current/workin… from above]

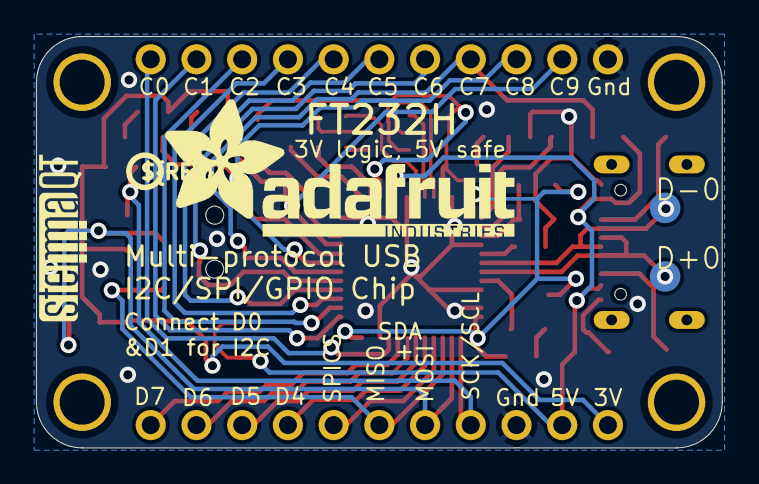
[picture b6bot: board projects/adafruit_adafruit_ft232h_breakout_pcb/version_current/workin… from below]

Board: 2 copper layers, 38.1 x 22.9 mm, 46 parts (5 on the bottom side), 40 nets.

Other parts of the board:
U$2: ADAFRUIT_3.5MM
U$3: ADAFRUIT_TEXT_20MM
U$8: STEMMAQT
U$11: PCBFEAT-REV-040
